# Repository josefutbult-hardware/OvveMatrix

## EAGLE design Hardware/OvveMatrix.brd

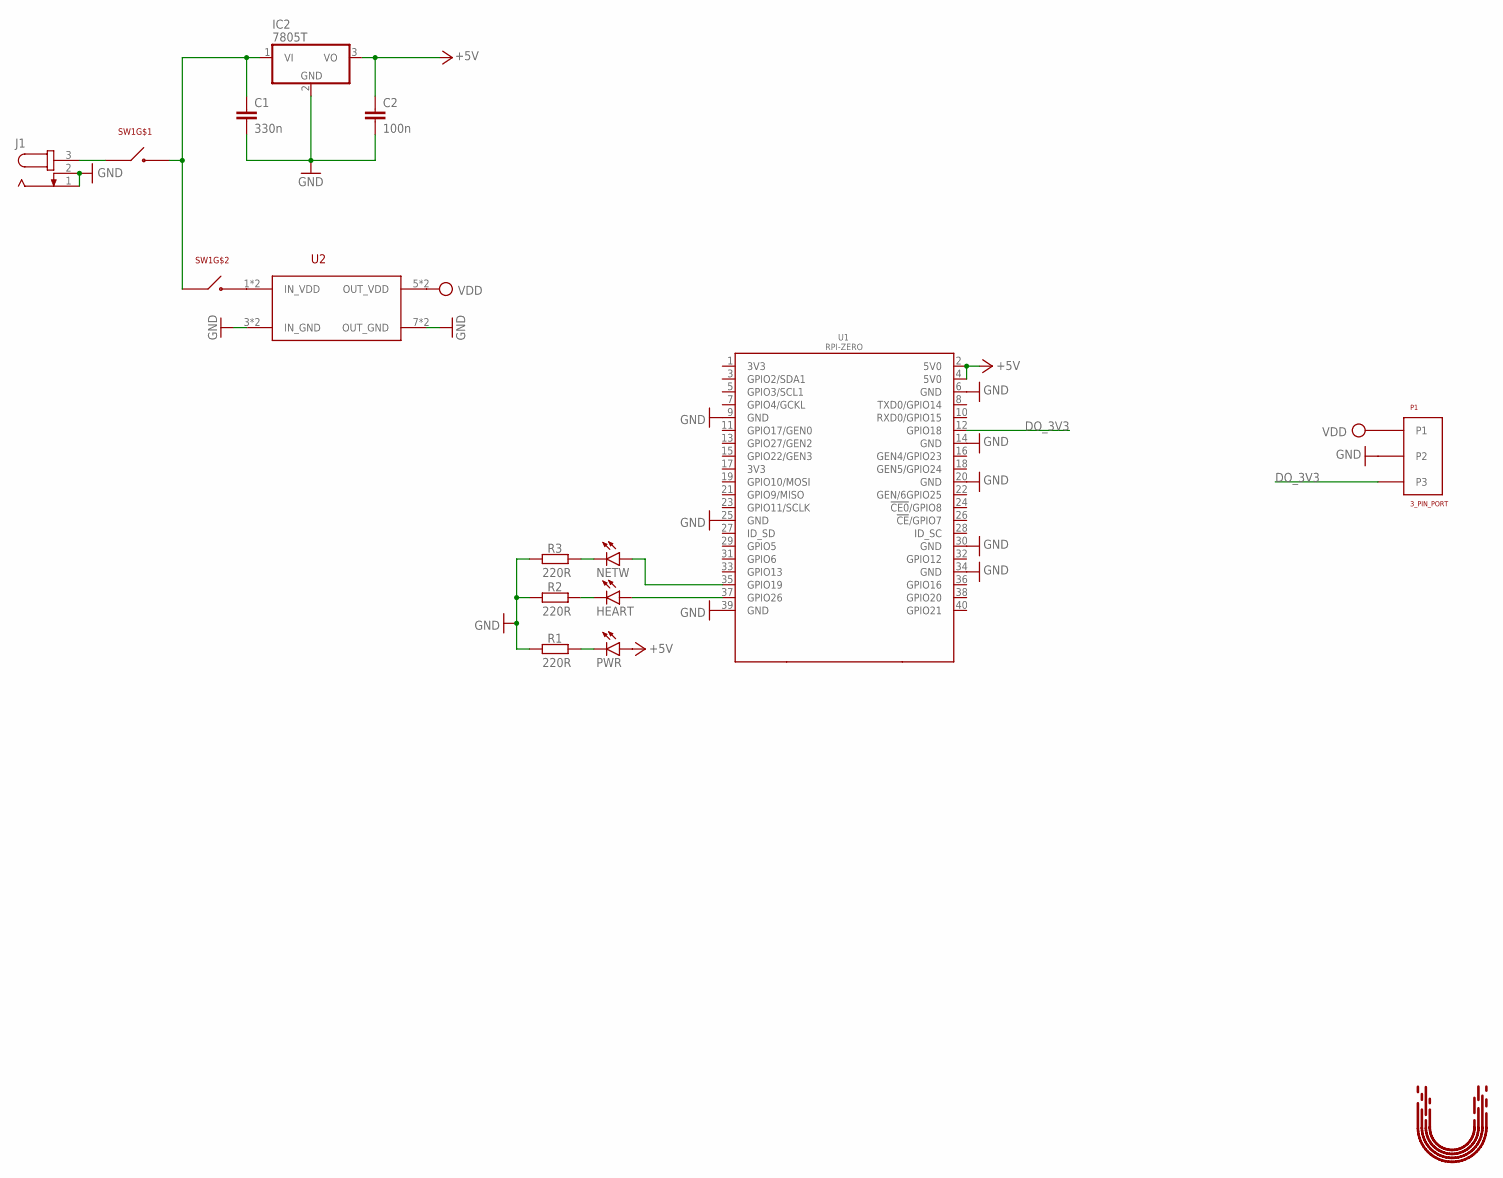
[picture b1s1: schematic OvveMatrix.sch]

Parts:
C1: 330n; C0805
C2: 100n; C0805
HEART: LEDLED_THROUGH; LED3MM
IC2: 7805T; TO220H
J1: JACK-PLUG0; SPC4077
NETW: LEDLED_THROUGH; LED3MM
P1: 3_PIN_PORT
PWR: LEDLED_THROUGH; LED3MM
R1, R2, R3: 220R; R0805
SW1: DOUBLE_SWITCH
U1: RPI-ZERO; RASPBERRYPI_BASTELSTUBE_V13_RASPI_BOARD_B+_FULL
U2: BUCK
U$1: UTBULT_DESIGN4; UD_4

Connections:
+5V: C2.1, IC2.3 (VO), PWR.A, U1.2 (5V0), U1.4 (5V0)
DO_3V3: P1.P$3 (P3), U1.12 (GPIO18)
GND: C1.2, C2.2, IC2.2 (GND), J1.1, J1.2, P1.P$2 (P2), R1.1, R2.1, R3.1, U1.6 (GND), U2.3 (IN_GND), U2.4 (IN_GND), U2.7 (OUT_GND), U2.8 (OUT_GND)
GND@1: U1.9 (GND)
GND@2: U1.25 (GND)
GND@3: U1.39 (GND)
GND@4: U1.14 (GND)
GND@5: U1.20 (GND)
GND@6: U1.30 (GND)
GND@7: U1.34 (GND)
unnamed: SW1.4 (3), U2.1 (IN_VDD), U2.2 (IN_VDD)
unnamed: NETW.K (C), R3.2
unnamed: HEART.K (C), R2.2
unnamed: HEART.A, U1.37 (GPIO26)
unnamed: PWR.K (C), R1.2
unnamed: C1.1, IC2.1 (VI), SW1.2 (3), SW1.3 (2)
unnamed: NETW.A, U1.35 (GPIO19)
unnamed: J1.3, SW1.1 (2)
VDD: P1.P$1 (P1), U2.5 (OUT_VDD), U2.6 (OUT_VDD)

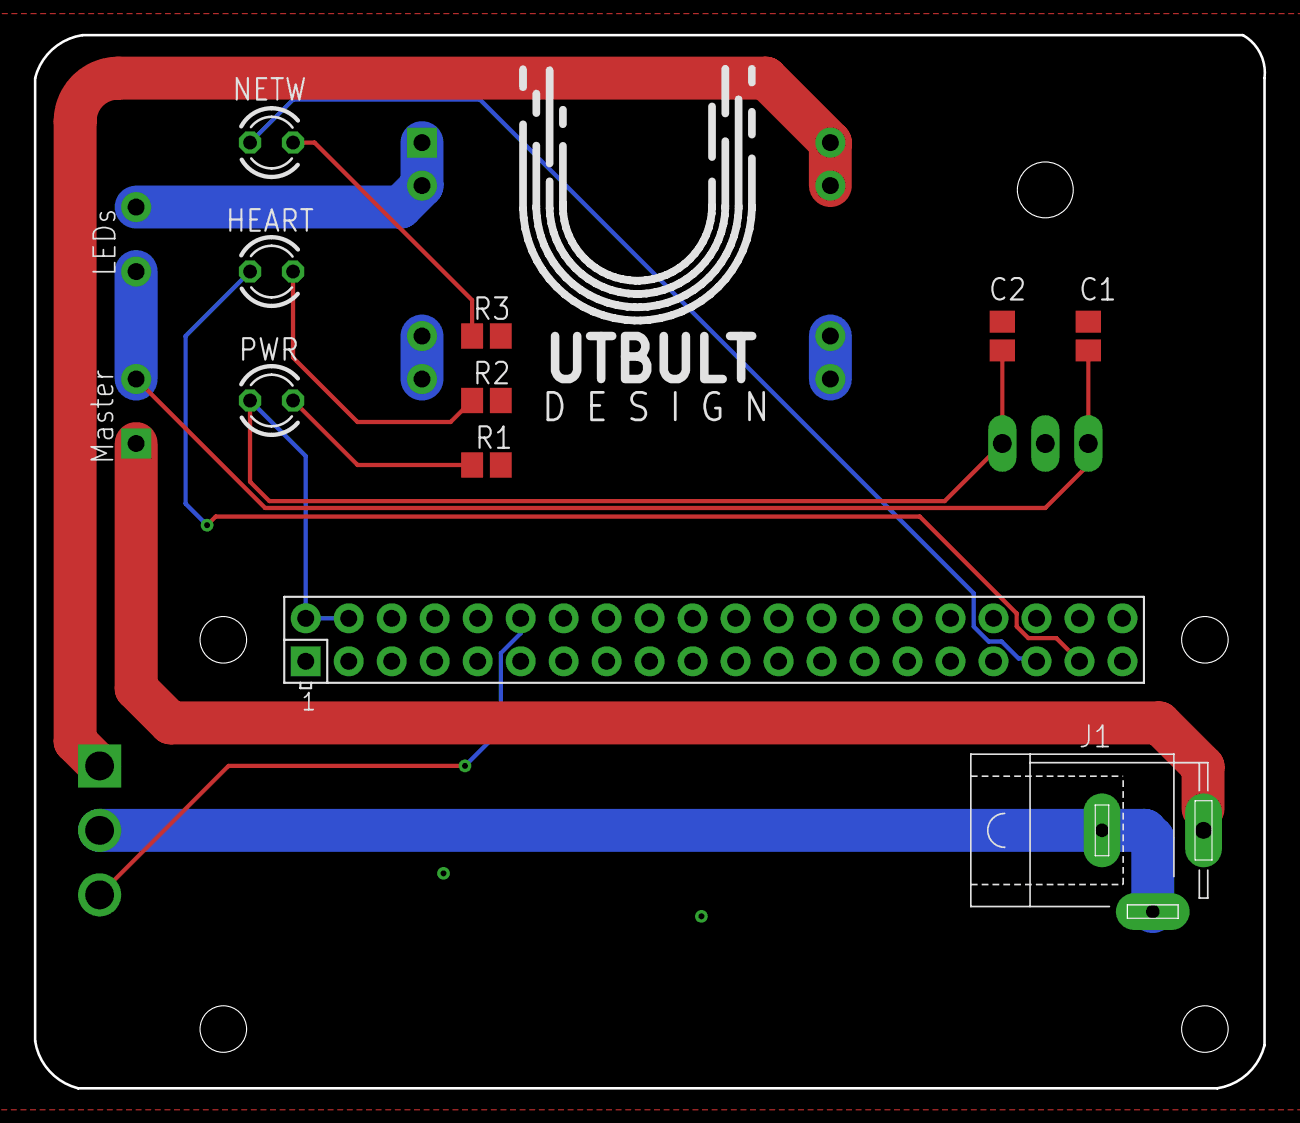
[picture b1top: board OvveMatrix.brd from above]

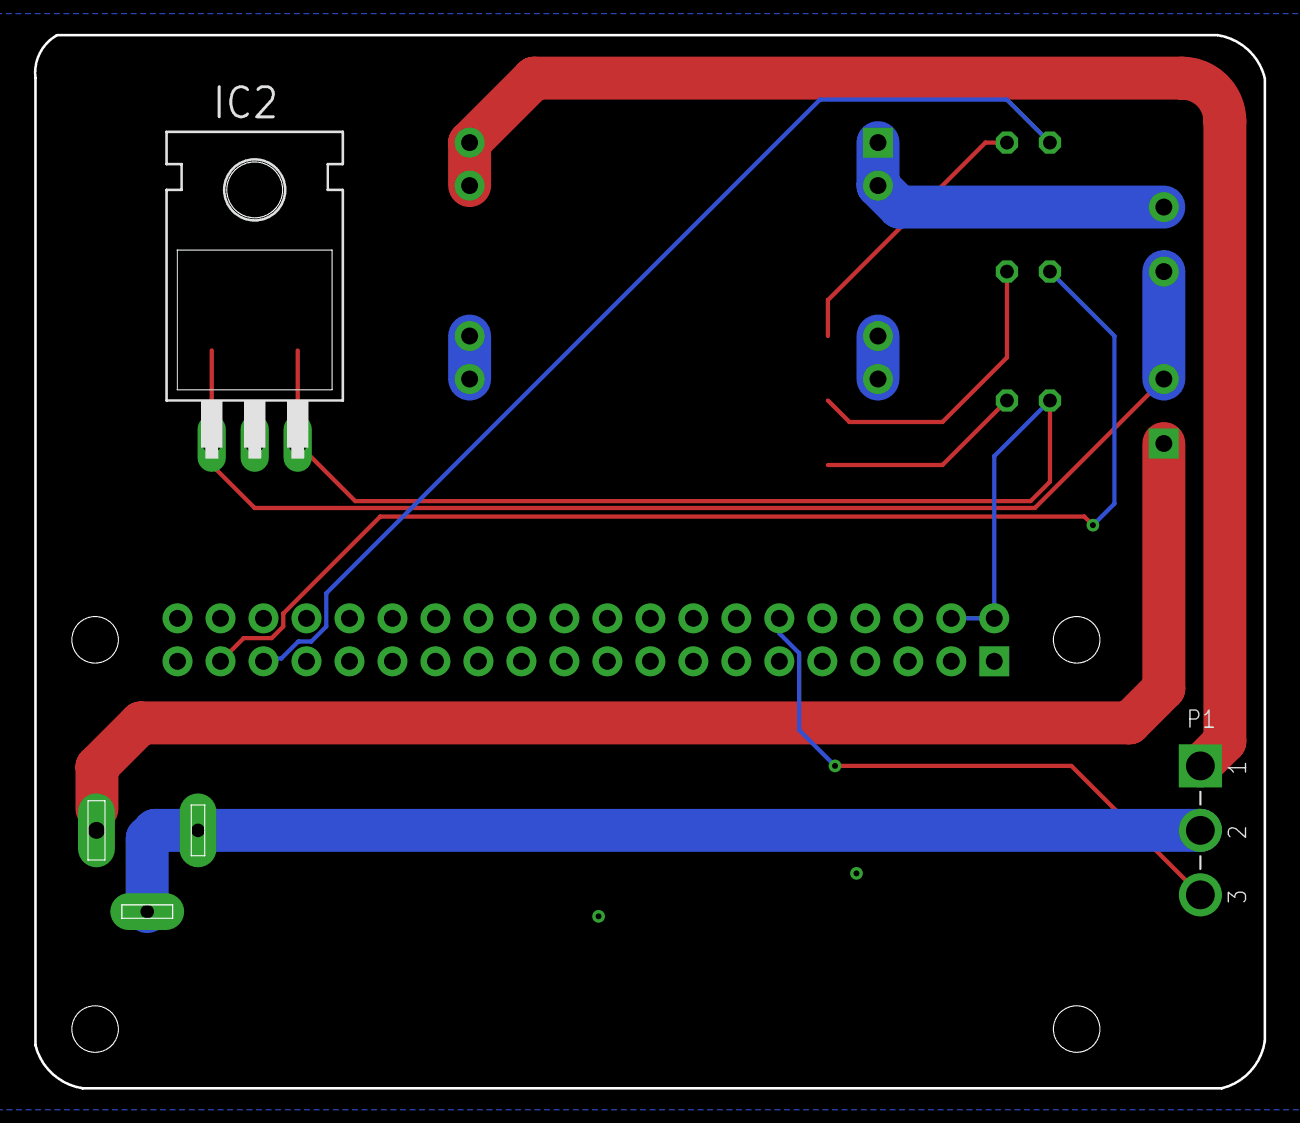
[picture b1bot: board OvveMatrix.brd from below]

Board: 2 copper layers, 72.7 x 62.2 mm, 15 parts (2 on the bottom side), 12 nets.

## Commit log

2021-08-29 Init
2021-08-31 Imported submodule
2021-09-02 Add ignore sublime stuff in gitignore
2021-09-02 Add Submodule
2021-09-04 Update client, and add functionality to server
